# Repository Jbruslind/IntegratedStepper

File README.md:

# IntegratedStepper
Integrated Stepper Motor Node

## Relevant Links
- [Annin AR3](https://robodk.com/robot/Annin-Robotics/AR3)
- [SimpleFOC](https://github.com/simplefoc/Arduino-FOC)
- [SimpleFOC CANCommander spec](https://docs.google.com/spreadsheets/d/1VWHshxOOnxZyKf5IjVzg1VQMbh7cPu5BULljX7UZJ8g)
- [CAN 2.0B spec](https://affon.narod.ru/CAN/CAN20B.pdf)
- [Waveshare USB CAN adapter](https://www.waveshare.com/usb-can-a.htm)
- [python-can docs](https://python-can.readthedocs.io/en/stable/)
- [Lemon Pepper Stepper](https://github.com/VIPQualityPost/lemon-pepper-stepper)
- [Simple-FOC-CAN](https://github.com/jkirsons/Simple-FOC-CAN.git)
- [SimpleFOC forums CAN megathread](https://community.simplefoc.com/t/can-bus-interface-simplefoc-standard-identifiers/577/32)
- [SimpleFOC Commander interface](https://docs.simplefoc.com/commander_interface)

## Gotchas
- 7 MSBs of Extended Format Base ID (ID-28 - ID-22) cannot all be recessive (CAN 2.0B spec, p. 13)

## Notes

CAN node to motor = one-to-many relationship -> bus id request has 0 motor id

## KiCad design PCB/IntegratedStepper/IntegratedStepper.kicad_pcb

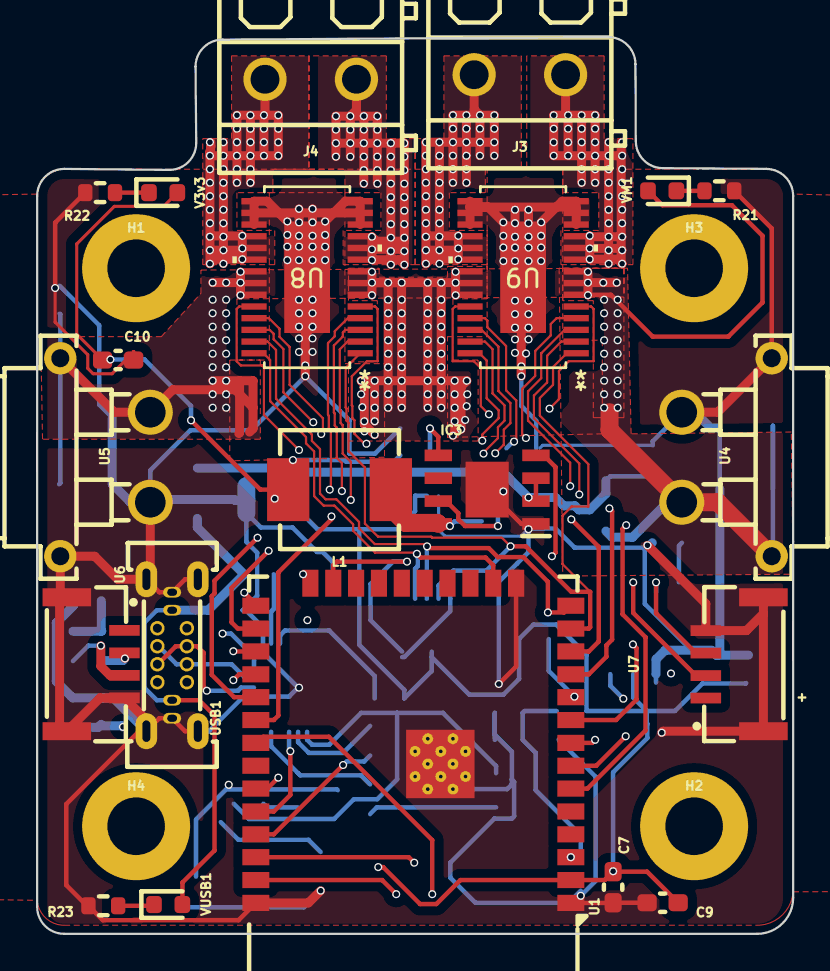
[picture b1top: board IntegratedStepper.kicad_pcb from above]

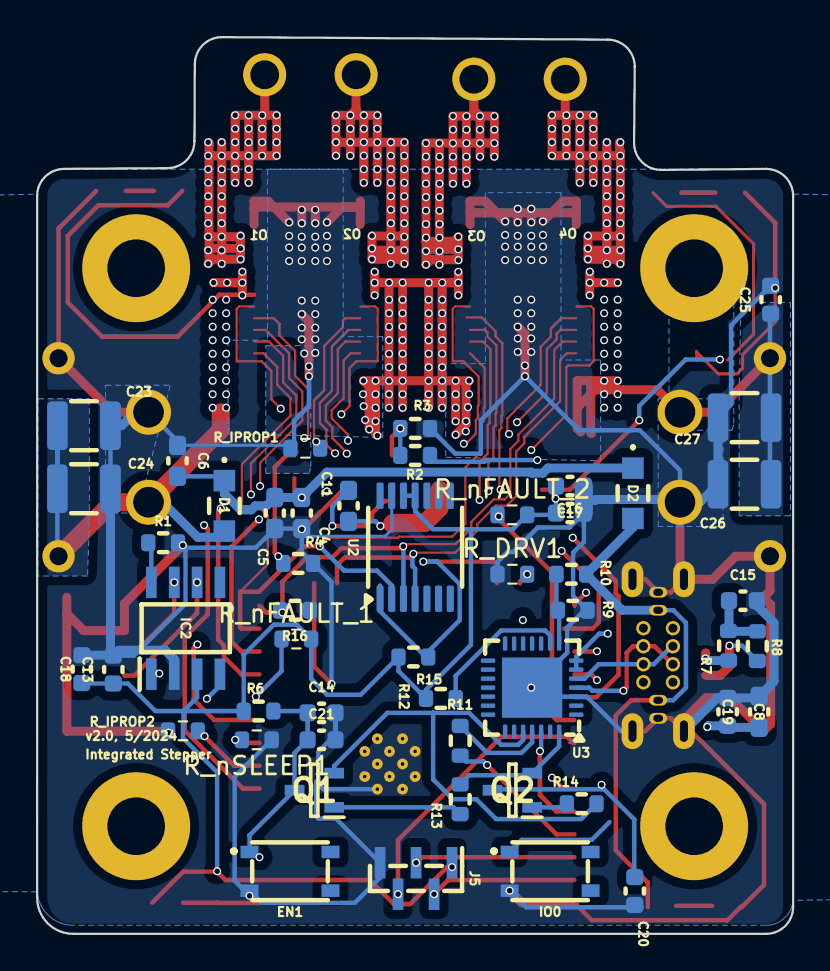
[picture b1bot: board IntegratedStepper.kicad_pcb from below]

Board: 4 copper layers, 42.0 x 49.8 mm, 75 parts (50 on the bottom side), 54 nets.

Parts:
C4, C7, C10: 10uf; C_0603_1608Metric_Pad1.08x0.95mm_HandSolder
C5, C9: 1uF; C_0603_1608Metric_Pad1.08x0.95mm_HandSolder
C6, C8: 100nf; C_0603_1608Metric_Pad1.08x0.95mm_HandSolder
C11: 0.1uF; C_0603_1608Metric_Pad1.08x0.95mm_HandSolder
C13, C14, C17, C18, C20, C21: 0.1uF; C_0603_1608Metric
C15: 4.7nF; C_0603_1608Metric
C16, C19, C25: 10uF; C_0603_1608Metric
C23: 22uF; C_1210_3225Metric
C24, C26, C27: 10uF; C_1210_3225Metric
D1, D2: PMEG6020ER,115; PMEG6020ER115
EN1: PTS815_SJG_250_SMTR_LFS; PTS815SJM250SMTRLFS
H1, H2, H3, H4: MountingHole_Pad; MountingHole_3.2mm_M3
IC2: SN65HVD230DR; SOT127P600X175-8N
IC3: LMR38020FSQDDARQ1; SOIC127P600X170-9N
IO0: PTS815_SJG_250_SMTR_LFS; PTS815SJM250SMTRLFS
J3, J4: Screw_Terminal_01x02; CONN-TH_P5.08_KF128-5.08-2P
J5: Conn_01x05_Socket; PinHeader_1x05_P1.00mm_Vertical_SMD_Pin1Left
L1: 10uH; IND-SMD_L7.2-W6.6_GPSR07X0
Q1, Q2: SS8050-G; SOT95P240X115-3N
R1, R13, R14, R15, R16, R21: 8.2k; R_0603_1608Metric
R2: 154k; R_0603_1608Metric
R3, R4: 64.9k; R_0603_1608Metric
R6: 10k; R_0603_1608Metric
R7, R8: 60; R_0603_1608Metric
R9: 47.5k; R_0603_1608Metric
R10: 22.1k; R_0603_1608Metric
R11: 10; R_0603_1608Metric
R12: 2k; R_0603_1608Metric
R22, R23: 500; R_0603_1608Metric
R_DRV1: 8.2k; R_0603_1608Metric
R_IPROP1, R_IPROP2: 820; R_0603_1608Metric
R_nFAULT_1, R_nFAULT_2: 8.2k; R_0603_1608Metric
R_nSLEEP1: 8.2k; R_0603_1608Metric
U1: ESP32-WROOM-32E; ESP32-WROOM-32D
U2: AS5048A; TSSOP-14_4.4x5mm_P0.65mm
U3: CP2102N-Axx-xQFN28; QFN-28-1EP_5x5mm_P0.5mm_EP3.35x3.35mm
U4, U5: XT30PW-F; CONN-TH_XT30PW-F-1
U6, U7: SM04B-GHS-TB(LF)(SN); CONN-SMD_4P-P1.25_SM04B-GHS-TB-LF-SN
U8, U9: PDRV8245SPWPQ1; U_PWP0028R_TEX
USB1: GT-USB-7038C; USB-C-TH_G-SWITCH_GT-USB-7038X
V3v3: LED; LED_0603_1608Metric
VM1: LED; LED_0603_1608Metric
VUSB1: LED; LED_0603_1608Metric

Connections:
3V3_VCC: C7.1, C8.1, C9.1, C10.1, C13.1, C16.1, C17.1, C18.1, C19.1, IC2.3 (VCC), J5.1, L1.2, R2.1, R6.1, R12.2, R15.2, R_nFAULT_1.2, R_nFAULT_2.2, U1.2 (VDD), U2.11 (VDD5V), U2.12 (VDD3V), U3.6 (VDD), U3.7 (VREGIN), V3v3.2 (A)
/3V3_VReg/VM: C23.1, C24.1, C25.1, C26.1, C27.1, D1.2 (A), U4.1, U4.4, U5.1, U5.4, U8.6 (VM), U8.7 (VM), U8.8 (VM), U8.21 (VM), U8.22 (VM), U8.23 (VM), U9.6 (VM), U9.7 (VM), U9.8 (VM), U9.21 (VM), U9.22 (VM), U9.23 (VM), VM1.2 (A)
/3V3_VReg/V_USB: D2.2 (A), R10.2, USB1.A4 (VBUS), USB1.A9 (VBUS), VUSB1.2 (A)
/CAN_Transciever/CAN_RX: IC2.4 (R), U1.28 (IO17)
/CAN_Transciever/CAN_TX: IC2.1 (D), U1.27 (IO16)
/DRV8245/DRV1_CS: U1.9 (IO33), U9.2 (NSCS)
/DRV8245/DRV2_CS: U1.33 (IO21), U8.2 (NSCS)
/DRV8245/DRVOFF: R_DRV1.2, U1.24 (IO2), U8.5 (DRVOFF), U9.5 (DRVOFF)
/DRV8245/M_MISO: R16.2, U1.14 (IO12), U2.3 (MISO), U8.27 (SDO), U9.27 (SDO)
/DRV8245/M_MOSI: U1.16 (IO13), U2.4 (MOSI), U8.28 (SDI), U9.28 (SDI)
/DRV8245/M_SCLK: U1.13 (IO14), U2.2 (CLK), U8.1 (SCLK), U9.1 (SCLK)
/DRV8245/NFAULT_1: R_nFAULT_1.1, U1.10 (IO25), U9.26 (NFAULT)
/DRV8245/NFAULT_2: R_nFAULT_2.1, U1.30 (IO18), U8.26 (NFAULT)
/DRV8245/NSLEEP: R_nSLEEP1.2, U1.8 (IO32), U8.24 (NSLEEP), U9.24 (NSLEEP)
/DRV8245/OUT1: J3.1, U9.9 (OUT1), U9.10 (OUT1), U9.11 (OUT1)
/DRV8245/OUT2: J3.2, U9.18 (OUT2), U9.19 (OUT2), U9.20 (OUT2)
/DRV8245/OUT3: J4.1, U8.9 (OUT1), U8.10 (OUT1), U8.11 (OUT1)
/DRV8245/OUT4: J4.2, U8.18 (OUT2), U8.19 (OUT2), U8.20 (OUT2)
/ESP32_MCU/ENC+: J5.3, U1.36 (IO22)
/ESP32_MCU/ENC-: J5.2, U1.37 (IO23)
/ESP32_MCU/ENC_IND: J5.4, U1.31 (IO19)
/ESP32_MCU/M_CS0: R15.1, U1.23 (IO15), U2.1 (~CSn)
CANH: IC2.6 (CANL), R7.1, U6.2, U7.2
CANL: IC2.7 (CANH), R8.2, U6.3, U7.3
DTR: Q2.2 (E), R13.1, U3.28 (~DTR)
EN: C14.1, C21.1, EN1.1 (COM_1), Q1.3 (C), R6.2, U1.3 (EN)
GND: C4.1, C5.1, C6.1, C7.2, C8.2, C9.2, C10.2, C13.2, C14.2, C15.2, C16.2, C17.2, C18.2, C19.2, C20.2, C21.2, C23.2, C24.2, C25.2, C26.2, C27.2, EN1.3 (NO_1), IC2.2 (GND), IC3.1 (GND), IC3.9 (EP), IO0.3 (NO_1), J5.5, R1.2, R3.2, R4.2, R9.2, R16.1, R21.1, R22.1, R23.1, R_DRV1.1, R_IPROP1.2, R_IPROP2.2, R_nSLEEP1.1, U1.1 (GND), U1.15 (GND), U1.38 (GND), U1.39 (GND), U2.13 (GND), U3.3 (GND), U3.29 (GND), U4.2, U4.3, U5.2, U5.3, U6.4, U6.5, U6.6, U7.4, U7.5, U7.6, U8.12 (GND), U8.13 (GND), U8.14 (GND), U8.15 (GND), U8.16 (GND), U8.17 (GND), U8.EPAD, U9.12 (GND), U9.13 (GND), U9.14 (GND), U9.15 (GND), U9.16 (GND), U9.17 (GND), U9.EPAD, USB1.13 (SHELL), USB1.A1 (GND), USB1.A12 (GND)
IN1: U1.11 (IO26), U9.4 (EN/IN1)
IN2: U1.12 (IO27), U9.3 (PH/IN2)
IN3: U1.29 (IO5), U8.4 (EN/IN1)
IN4: U1.26 (IO4), U8.3 (PH/IN2)
IO0: C20.1, IO0.1 (COM_1), Q2.3 (C), U1.25 (IO0)
IPROPI_1: R_IPROP1.1, U1.6 (IO34), U9.25 (IPROPI)
IPROPI_2: R_IPROP2.1, U1.7 (IO35), U8.25 (IPROPI)
unnamed: C15.1, R7.2, R8.1
unnamed: IC2.8 (RS), R1.1
unnamed: C11.1, IC3.7 (BOOT)
unnamed: IC3.5 (FB), R2.2, R3.1
unnamed: IC3.4 (RT/SYNC), R4.1
unnamed: C11.2, IC3.8 (SW), L1.1
unnamed: Q1.1 (B), R13.2
unnamed: Q2.1 (B), R14.2
unnamed: R11.2, U1.35 (TXD0/IO1)
unnamed: R9.1, R10.1, U3.8 (VBUS)
unnamed: R12.1, U3.9 (~RST)
unnamed: R22.2, V3v3.1 (K)
unnamed: R21.2, VM1.1 (K)
unnamed: R23.2, VUSB1.1 (K)
RTS: Q1.2 (E), R14.1, U3.24 (~RTS)
RX: U1.34 (RXD0/IO3), U3.26 (TXD)
TX: R11.1, U3.25 (RXD)
USB_D+: U3.4 (D+), USB1.A6 (Dp1), USB1.B6 (Dp2)
USB_D-: U3.5 (D-), USB1.A7 (Dn1), USB1.B7 (Dn2)
VIN: C4.2, C5.2, C6.2, D1.1 (K), D2.1 (K), IC3.2 (EN), IC3.3 (VIN)

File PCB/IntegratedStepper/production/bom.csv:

Designator,Footprint,Quantity,Value,LCSC Part #
"C10, C16, C19, C25, C4, C7",0603,6,10uf,C96446
C11,0603,1,0.1uF,C14663
"C13, C14, C17, C18, C20, C21",0603,6,0.1uF,C5186689
C23,1210,1,22uF,C2929200
"C24, C26, C27",1210,3,10uF,C2929200
"C5, C9",0603,2,1uF, C15849
"C6, C8",0603,2,100nf,C14663
"D1, D2",PMEG6020ER115,2,"PMEG6020ER,115",C98663
"EN1, IO0",PTS815SJM250SMTRLFS,2,PTS815_SJG_250_SMTR_LFS,C411883
IC2,SOT127P600X175-8N,1,SN65HVD230DR,C12084
IC3,SOIC127P600X170-9N,1,LMR38020FSQDDARQ1,C5149193
"J3, J4",CONN-TH_P5.08_KF128-5.08-2P,2,Screw_Terminal_01x02,C474952
L1,IND-SMD_L7.2-W6.6_GPSR07X0,1,10uH,C5189959
"Q1, Q2",SOT95P240X115-3N,2,SS8050-G,C916392
"R1, R13, R14, R15, R16, R21, R_DRV1, R_nFAULT_1, R_nFAULT_2, R_nSLEEP1",0603,10,8.2k,C25981
R10,0603,1,22.1k,C2989573
R11,0603,1,10,C177687
R12,0603,1,2k,C217936
R2,0603,1,154k,C425661
"R22, R23",0603,2,500,C2989147
"R3, R4",0603,2,64.9k, C912530
R6,0603,1,10k,C469659
R9,0603,1,47.5k,C319608
"R_IPROP1, R_IPROP2",0603,2,820,C23253
U1,ESP32-WROOM-32D,1,ESP32-WROOM-32E,C701341
U2,TSSOP-14_4.4x5mm_P0.65mm,1,AS5048A,C2655181
U3,QFN-28-1EP_5x5mm_P0.5mm_EP3.35x3.35mm,1,CP2102N-Axx-xQFN28,C964632
"U4, U5",CONN-TH_XT30PW-F-1,2,XT30PW-F,C2913282
"U6, U7",CONN-SMD_4P-P1.25_SM04B-GHS-TB-LF-SN,2,SM04B-GHS-TB(LF)(SN),C189895
"U8, U9",U_PWP0028R_TEX,2,PDRV8245SPWPQ1,
USB1,USB-C-TH_G-SWITCH_GT-USB-7038X,1,GT-USB-7038C,C2982476
"V3v3, VM1, VUSB1",0603,3,LED,C965804

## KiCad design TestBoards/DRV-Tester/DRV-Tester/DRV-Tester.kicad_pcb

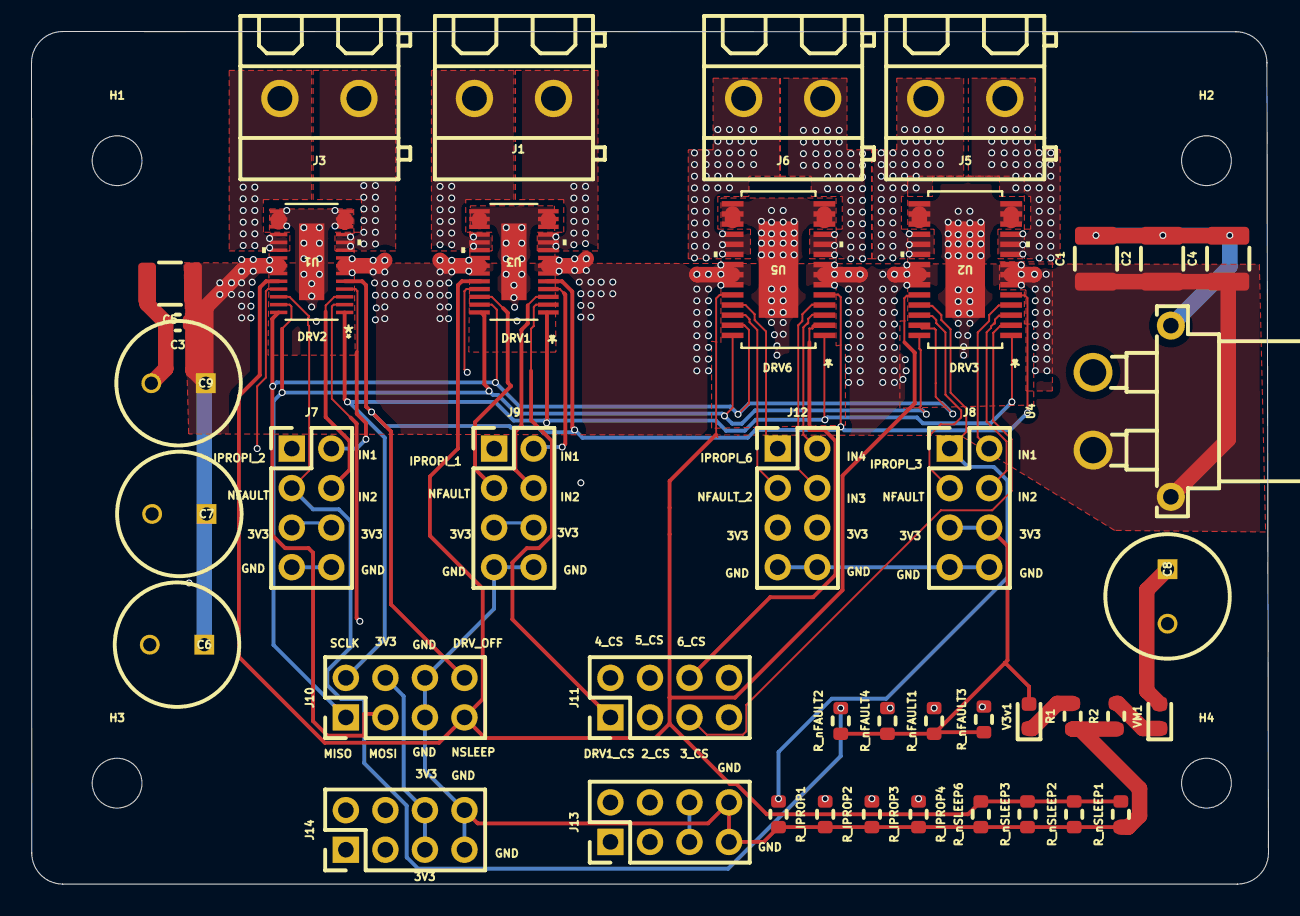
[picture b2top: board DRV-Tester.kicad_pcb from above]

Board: 4 copper layers, 79.5 x 54.8 mm, 46 parts (0 on the bottom side), 38 nets.

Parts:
C1: 22uF; C_1210_3225Metric
C2, C4, C5: 10uF; C_1210_3225Metric
C3: 10uF; C_0603_1608Metric
C6, C7, C8, C9: EEU-FC1J101LB; CAPPRD350W65D800H1650
H1, H2, H3, H4: MountingHole_Pad; MountingHole_3.2mm_M3
J1, J3, J5, J6: Screw_Terminal_01x02; CONN-TH_P5.08_KF128-5.08-2P
J7, J8, J9, J10, J11, J12, J13, J14: Conn_02x04_Odd_Even; PinHeader_2x04_P2.54mm_Vertical
R1: 500; R_0603_1608Metric
R2: 8.2k; R_0603_1608Metric
R_IPROP1, R_IPROP2, R_IPROP3, R_IPROP4: 820; R_0603_1608Metric
R_nFAULT1, R_nFAULT2, R_nFAULT3, R_nFAULT4: 820; R_0603_1608Metric
R_nSLEEP1, R_nSLEEP2, R_nSLEEP3, R_nSLEEP6: 8.2k; R_0603_1608Metric
U1: PDRV8244SPWPQ1; U_DGQ0028A_TEX-L
U2, U5: PDRV8245SPWPQ1; U_PWP0028R_TEX
U3: PDRV8243SPWPQ1; VSSOP_SDGQQ1_TEX
U4: XT30PW-F; CONN-TH_XT30PW-F-1
V3v1: LED; LED_0603_1608Metric
VM1: LED; LED_0603_1608Metric

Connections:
3V3: J7.5, J7.6, J8.5, J8.6, J9.5, J9.6, J10.4, J12.5, J12.6, J13.5, J13.6, J14.5, J14.6, R_nFAULT1.1, R_nFAULT2.1, R_nFAULT3.1, R_nFAULT4.1, V3v1.2 (A)
/DRV1_GPIO1/IN1: J7.2, U1.4 (EN/IN1)
/DRV1_GPIO1/IN2: J7.4, U1.3 (PH/IN2)
/DRV1_GPIO1/N_FAULT: J7.3, R_nFAULT2.2, U1.26 (NFAULT)
/DRV1_GPIO2/IN1: J9.2, U3.4 (EN/IN1)
/DRV1_GPIO2/IN2: J9.4, U3.3 (PH/IN2)
/DRV1_GPIO2/N_FAULT: J9.3, R_nFAULT1.2, U3.26 (NFAULT)
/DRV1_GPIO/IN1: J8.2, U2.4 (EN/IN1)
/DRV1_GPIO/IN2: J8.4, U2.3 (PH/IN2)
/DRV1_GPIO/IN3: J12.4, U5.4 (EN/IN1)
/DRV1_GPIO/IN4: J12.2, U5.3 (PH/IN2)
/DRV1_GPIO/N_FAULT: J8.3, R_nFAULT3.2, U2.26 (NFAULT)
/DRV1_GPIO/N_FAULT2: J12.3, R_nFAULT4.2, U5.26 (NFAULT)
/DRV8243/OUT1: J1.1, U3.9 (OUT1), U3.10 (OUT1), U3.11 (OUT1)
/DRV8243/OUT2: J1.2, U3.18 (OUT2), U3.19 (OUT2), U3.20 (OUT2)
/DRV8244/OUT1: J3.1, U1.9 (OUT1), U1.10 (OUT1), U1.11 (OUT1)
/DRV8244/OUT2: J3.2, U1.18 (OUT2), U1.19 (OUT2), U1.20 (OUT2)
/DRV8245/OUT1: J5.1, U2.9 (OUT1), U2.10 (OUT1), U2.11 (OUT1)
/DRV8245/OUT2: J5.2, U2.18 (OUT2), U2.19 (OUT2), U2.20 (OUT2)
/DRV8245/OUT3: J6.1, U5.9 (OUT1), U5.10 (OUT1), U5.11 (OUT1)
/DRV8245/OUT4: J6.2, U5.18 (OUT2), U5.19 (OUT2), U5.20 (OUT2)
DRV1_CS: J11.1, U3.2 (NSCS)
DRV2_CS: J11.3, U1.2 (NSCS)
DRV3_CS: J11.5, U2.2 (NSCS)
DRV6_CS: J11.6, U5.2 (NSCS)
DRV_OFF: J10.8, U1.5 (DRVOFF), U2.5 (DRVOFF), U3.5 (DRVOFF), U5.5 (DRVOFF)
GND: C1.2, C2.2, C3.2, C4.2, C5.2, C6.2 (-), C7.2 (-), C8.2 (-), C9.2 (-), J7.7, J7.8, J8.7, J8.8, J9.7, J9.8, J10.5, J10.6, J12.7, J12.8, J13.7, J13.8, J14.7, J14.8, R1.1, R2.1, R_IPROP1.2, R_IPROP2.2, R_IPROP3.2, R_IPROP4.2, R_nSLEEP1.1, R_nSLEEP2.1, R_nSLEEP3.1, R_nSLEEP6.1, U1.12 (GND), U1.13 (GND), U1.14 (GND), U1.15 (GND), U1.16 (GND), U1.17 (GND), U1.EPAD, U2.12 (GND), U2.13 (GND), U2.14 (GND), U2.15 (GND), U2.16 (GND), U2.17 (GND), U2.EPAD, U3.12 (GND), U3.13 (GND), U3.14 (GND), U3.15 (GND), U3.16 (GND), U3.17 (GND), U3.EPAD, U4.2, U4.3, U5.12 (GND), U5.13 (GND), U5.14 (GND), U5.15 (GND), U5.16 (GND), U5.17 (GND), U5.EPAD
IPROPI_1: J9.1, R_IPROP3.1
IPROPI_2: J7.1, R_IPROP2.1, U1.25 (IPROPI), U3.25 (IPROPI)
IPROPI_3: J8.1, R_IPROP1.1, U2.25 (IPROPI)
IPROPI_6: J12.1, R_IPROP4.1, U5.25 (IPROPI)
M_MISO: J10.1, U1.27 (SDO), U2.28 (SDI), U3.28 (SDI), U5.28 (SDI)
M_MOSI: J10.3, U1.28 (SDI), U2.27 (SDO), U3.27 (SDO), U5.27 (SDO)
M_SCLK: J10.2, U1.1 (SCLK), U2.1 (SCLK), U3.1 (SCLK), U5.1 (SCLK)
NSLEEP: J10.7, R_nSLEEP1.2, R_nSLEEP2.2, R_nSLEEP3.2, R_nSLEEP6.2, U1.24 (NSLEEP), U2.24 (NSLEEP), U3.24 (NSLEEP), U5.24 (NSLEEP)
unnamed: R1.2, V3v1.1 (K)
unnamed: R2.2, VM1.1 (K)
VM: C1.1, C2.1, C3.1, C4.1, C5.1, C6.1 (+), C7.1 (+), C8.1 (+), C9.1 (+), U1.6 (VM), U1.7 (VM), U1.8 (VM), U1.21 (VM), U1.22 (VM), U1.23 (VM), U2.6 (VM), U2.7 (VM), U2.8 (VM), U2.21 (VM), U2.22 (VM), U2.23 (VM), U3.6 (VM), U3.7 (VM), U3.8 (VM), U3.21 (VM), U3.22 (VM), U3.23 (VM), U4.1, U4.4, U5.6 (VM), U5.7 (VM), U5.8 (VM), U5.21 (VM), U5.22 (VM), U5.23 (VM), VM1.2 (A)

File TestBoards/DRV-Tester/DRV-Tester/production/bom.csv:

Designator,Footprint,Quantity,Value,LCSC Part #
C1,1210,1,22uF,C2929200
"C2, C4, C5",1210,3,10uF,C2929200
C3,0603,1,10uF,C96446
"C6, C7, C8, C9",CAPPRD350W65D800H1650,4,EEU-FC1J101LB,
"J1, J3, J5, J6",CONN-TH_P5.08_KF128-5.08-2P,4,Screw_Terminal_01x02,C474952
"J10, J11, J12, J13, J14, J7, J8, J9",PinHeader_2x04_P2.54mm_Vertical,8,Conn_02x04_Odd_Even,
R1,0603,1,500,C2989147
"R2, R_nSLEEP1, R_nSLEEP2, R_nSLEEP3, R_nSLEEP6",0603,5,8.2k,C25981
"R_IPROP1, R_IPROP2, R_IPROP3, R_IPROP4, R_nFAULT1, R_nFAULT2, R_nFAULT3, R_nFAULT4",0603,8,820,C23253
U1,U_DGQ0028A_TEX-L,1,PDRV8244SPWPQ1,
"U2, U5",U_PWP0028R_TEX,2,PDRV8245SPWPQ1,
U3,VSSOP_SDGQQ1_TEX,1,PDRV8243SPWPQ1,
U4,CONN-TH_XT30PW-F-1,1,XT30PW-F,C2913282
"V3v1, VM1",0603,2,LED,C965804

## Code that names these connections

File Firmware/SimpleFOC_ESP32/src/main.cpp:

#include <SimpleFOC.h>
#include <drv824x_driver.h>
// #include <SimpleFOCCAN.h>

#define CAN_TX 16
#define CAN_RX 17

#define nSLEEP 32
#define DRVOFF 2

#define nFAULT_1 25
#define nFAULT_2 18

#define IPROPI_1 33
#define IPROPI_2 35

#define A_p 1/3070
#define R_IPROP 820

TaskHandle_t moveMotors;
void moveMotorsfun( void * pvParameters);
// Stepper motor instance
StepperMotor motor = StepperMotor(50);
SPIClass* hspi = new SPIClass(HSPI); 
// Stepper driver instance
// DRV824X_2PH(int ph1A,int ph1B, int en = NOT_SET, int nsleep = NOT_SET, int nCS = NOT_SET,
//     SPISettings settings = DRV824xSPISettings, SPIClass* _spi = &SPI);
DRV824X_2PH driver_1 = DRV824X_2PH(26, 27, 33, DRV824xSPISettings, hspi);
DRV824X_2PH driver_2 = DRV824X_2PH(4, 5, 21, DRV824xSPISettings, hspi);


DRV824X_4PH driver = DRV824X_4PH(driver_1, driver_2);
MagneticSensorSPI sensor = MagneticSensorSPI(AS5048_SPI, 15);


// LowsideCurrentSense current_sense = LowsideCurrentSense(A_p, R_IPROP, IPROPI_1, IPROPI_2);

// CANDriver can = CANDriver(CAN_TX, CAN_RX);
// CANCommander canCommand = CANCommander(can);
Commander command = Commander(Serial);

void onMotor(char* cmd){ command.motor(&motor, cmd); }
// void doCommanderCAN(char* cmd) { canCommand.motor(&motor, cmd); }

void setup() {
  Serial.begin(115200);
  Serial.print("RUNNING ON CORE: ");
  Serial.println(xPortGetCoreID());

  pinMode(nSLEEP, OUTPUT);
  pinMode(DRVOFF, OUTPUT);

  digitalWrite(nSLEEP, HIGH);
  digitalWrite(DRVOFF, LOW);

  disableCore0WDT();
  xTaskCreatePinnedToCore(
                      moveMotorsfun,   /* Task function. */
                      "Command Motors",     /* name of task. */
                      100000,       /* Stack size of task */
                      NULL,        /* parameter of the task */
                      2,           /* priority of the task */
                      &moveMotors,      /* Task handle to keep track of created task */
                      0);          /* pin task to core 0 */                  
  delay(500); 

  // define the motor id
    // comment out if not needed
  motor.useMonitoring(Serial);
  command.add('M', onMotor, "motor");
  // canCommand.add('M', doCommanderCAN, (char*)"motor");

  _delay(1000);
}


void moveMotorsfun( void * pvParameters) {
  motor.voltage_sensor_align = 5;
  // pwm frequency to be used [Hz]
  // driver.pwm_frequency = 20000;
  // power supply voltage [V]
  driver.voltage_power_supply = 19;
  // Max DC voltage allowed - default voltage_power_supply

  // ##################### ENCODER CONFIG
  // encoder.quadrature = Quadrature::ON;

  // encoder.pullup = Pullup::USE_INTERN;
  // encoder.init();
  // encoder.enableInterrupts(doA, doB);
  // motor.linkSensor(&encoder);

  // ##################### I2C CONFIG
  // sensor.init();
  // motor.linkSensor(&sensor);

  // ##################### SPI CONFIG
  sensor.init(hspi);
  motor.linkSensor(&sensor);


  // choose FOC modulation
  motor.foc_modulation = FOCModulationType::SinePWM;
  motor.torque_controller = TorqueControlType::voltage;
  motor.controller = MotionControlType::angle_openloop;

  // power supply voltage [V]
  driver.voltage_power_supply = 19;
  // motor.motion_downsample = 2;
  // printf("Driver1 config2: %x \n", driver.driver1.getConfig2().data);
  // printf("Driver1 config3: %x \n", driver.driver1.getConfig3().data);
  // printf("Driver1 config4: %x \n", driver.driver1.getConfig4().data);

  driver.init();

  // link the motor to the sensor
  motor.linkDriver(&driver);

  // set control loop type to be used]
  
  driver.pwm_frequency = 20000;
  driver.voltage_limit = driver.voltage_power_supply / 2;
  motor.voltage_limit = driver.voltage_power_supply / 2;
  
  // controller configuration based on the control type 
  motor.PID_velocity.P = 2;
  motor.PID_velocity.I = 20;
  motor.PID_velocity.D = 0;
  motor.LPF_velocity.Tf = 0.009;

  // angle loop controller
  motor.P_angle.P = 20;
  motor.P_angle.D = 0;
  // angle loop velocity limit
  motor.velocity_limit = 5;
  motor.current_limit = 4;
  motor.phase_resistance = 0.9;
  motor.phase_inductance = 0.00280;
  
  
  // use monitoring with serial for motor init
  // monitoring port
  
  // current_sense.linkDriver(&driver);
  // current_sense.init();

  motor.monitor_downsample = 1000;
  // initialise motor
  motor.monitor_variables =  _MON_TARGET | _MON_VOLT_Q | _MON_VOLT_D | _MON_VEL | _MON_ANGLE; 
  motor.init();
  // align encoder and start FOC
  motor.initFOC();

  printf("Driver2: %x \n", driver.driver2.getDeviceID());
  printf("Driver2 fault: %x \n", driver.driver2.getFault());
  printf("Driver2 config1: %x \n", driver.driver2.getConfig1().data);

  printf("Driver1: %x \n", driver.driver1.getDeviceID());
  printf("Driver1 fault: %x \n", driver.driver1.getFault());
  printf("Driver1 config1: %x \n", driver.driver1.getConfig1().data);

    for(;;){
        //This function keeps motors spinning and must be run as fast as possible
        motor.move();
        motor.loopFOC();
    }
}

void loop() {
  command.run();
  // motor.monitor();
  if((driver.driver1.getStatus1().status.FAULT || driver.driver2.getStatus1().status.FAULT) && !(driver.driver1.getStatus1().status.SPI_ERR || driver.driver2.getStatus1().status.SPI_ERR))
  {
    printf("MOTOR FAULT | M1 %x | M2 %x \n", driver.driver1.getStatus1().data, 
    driver.driver2.getStatus1().data);
    if(driver.driver1.getStatus1().status.TSD || driver.driver2.getStatus1().status.TSD){
      printf("OVERTEMP!!! Waiting to cool down \n");
    }
    else{
      driver.clear();
    }
    
  }
  // canCommand.runWithCAN();
}

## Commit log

2024-04-19 import: github.com/Jbruslind/PersonalProjects.git [2c92b14/IntegratedStepper]
2024-04-19 doc: add links to README
2024-04-19 Move files to individual repo
2024-04-19 controller: init(all)
2024-04-19 docs(controller): update README with instructions for Plebian users
2024-04-22 add NEMA 17 adapter for drivers
2024-05-05 init PCB dev area
2024-05-10 Update PCB with DRV8243 for 12A capacity
2024-05-14 update layout temp
2024-05-14 update layout to XT30 + 3.5mm Jack
2024-05-15 update layout with pinout changes
2024-05-16 finalize layout w/ thermals
2024-05-20 Update final layout, replace CAN w/ JST
2024-06-02 update code for v2
2024-06-05 update main loop to have fault features
2024-06-10 add test board PCB
2024-06-12 update new tester board sch
2024-06-14 update new layout with DRV8245
2024-06-15 update layout for larger pcb
2024-06-16 Update semi-final layout for HVSSOP DRV8245
2024-06-17 update tester board with layout
2024-06-18 finish layout for stupid lil test board
2024-06-19 add caps and LEDs to testboard
2024-07-03 Create initial driver for DRV824x drivers for ESP32 / SimpleFOC
2024-07-04 update driver to be modular based on single DRV
2024-07-07 update more functions for config regs
2024-07-07 updated CS to be on IO instead of just input pin
2024-07-10 update pinout for ESP32
